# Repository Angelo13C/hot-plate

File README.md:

# Hot plate
An hot plate used to reflow solder electrical components on a PCB.

This is a table of contents:

| Name  | Description |
| ------------- | ------------- |
| [Firmware](firmware)  | The software running on the hot plate, written in Rust  |
| [Electronics](electronics)  | The plate that will become hot (which is a PCB) and the controller board that controls the current going to the plate (a separate PCB based on a STM32 microcontroller)   |

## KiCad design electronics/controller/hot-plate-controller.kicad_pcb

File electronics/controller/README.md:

# Electronics
This is the electrical control board on which the firmware runs.

It's based on an `STM32F730R8T6`. The board receives stable `24V` from an external power supply unit and requires around `10A` of current.

On the board there's a switching regulator that converts the `24V` to `3.3V`, which is used by: `thermistors`, `display`, `MLX90614` and microcontroller.

## Schematic
This is the electrical schematic of the board:

## PCB
The PCB (dimensions: 52mm x 52mm) has 4 layers (PWR/SIGNAL, GND, GND, PWR/SIGNAL). This is an image of the top layer:

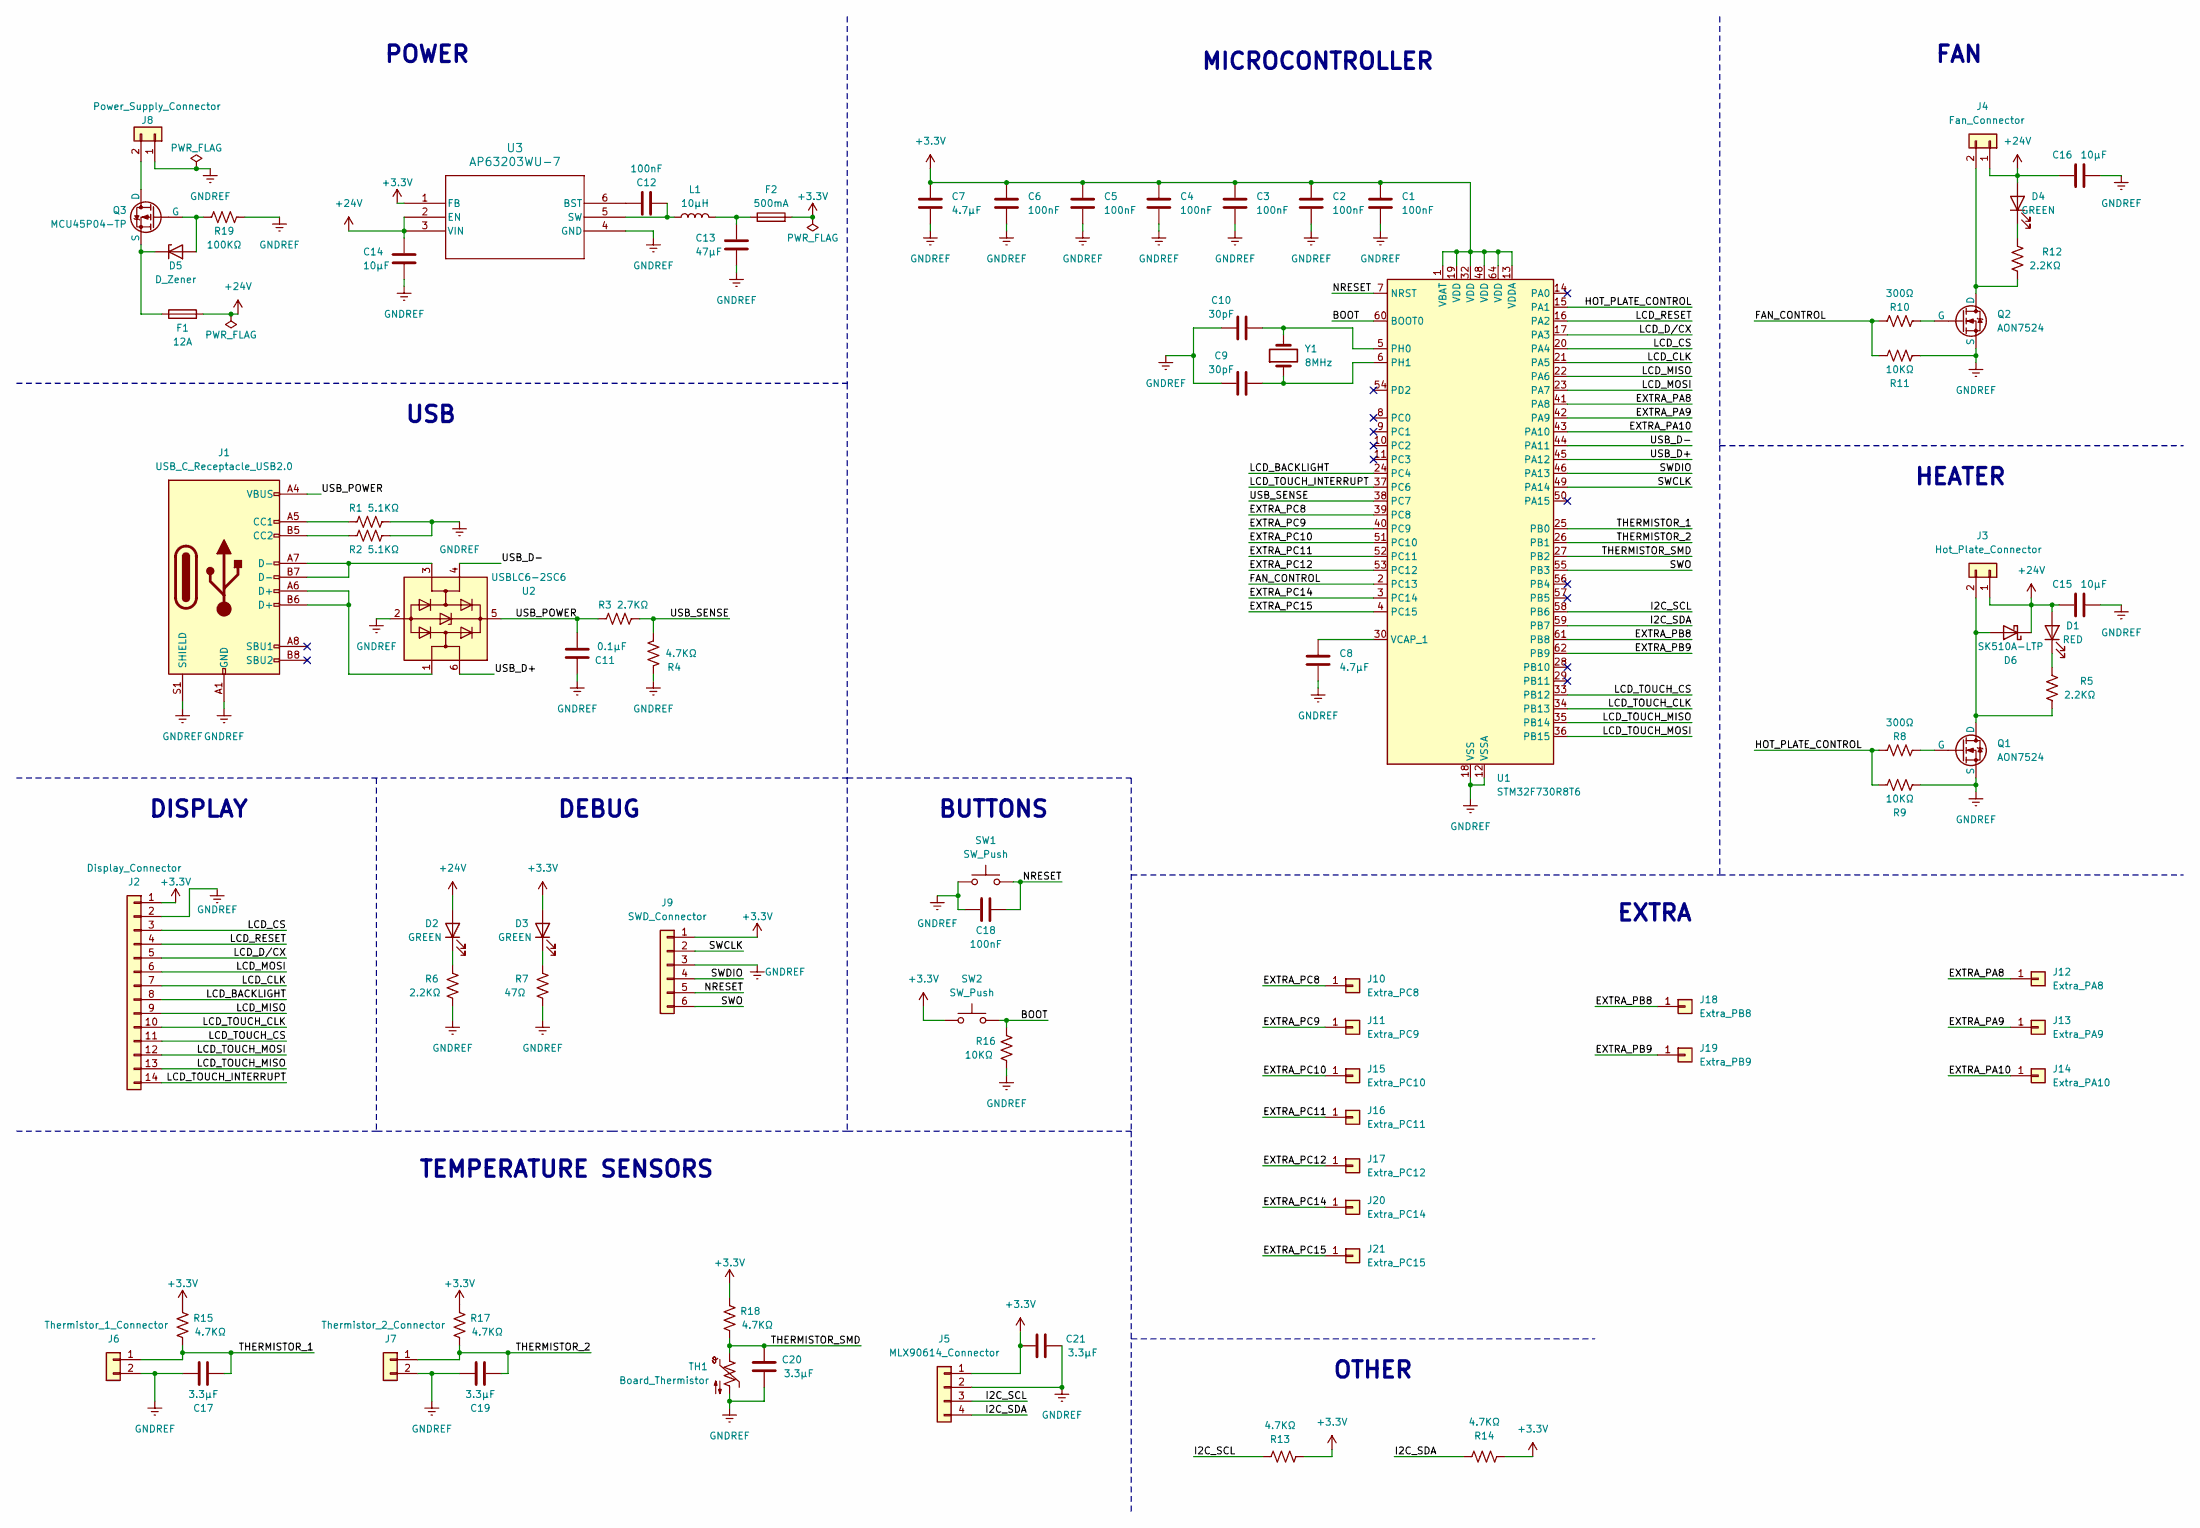
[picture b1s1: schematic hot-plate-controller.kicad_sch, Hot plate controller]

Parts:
C1, C2, C3, C4, C5, C6, C12, C18: 100nF; C_0805_2012Metric_Pad1.18x1.45mm_HandSolder
C7, C8: 4.7μF; C_0805_2012Metric_Pad1.18x1.45mm_HandSolder
C9, C10: 30pF; C_0805_2012Metric_Pad1.18x1.45mm_HandSolder
C11: 0.1μF; C_0805_2012Metric_Pad1.18x1.45mm_HandSolder
C13: 47μF; C_0805_2012Metric_Pad1.18x1.45mm_HandSolder
C14, C15, C16: 10μF; C_0805_2012Metric_Pad1.18x1.45mm_HandSolder
C17, C19, C20, C21: 3.3μF; C_0805_2012Metric_Pad1.18x1.45mm_HandSolder
D1: RED; LED_0603_1608Metric_Pad1.05x0.95mm_HandSolder
D2, D3, D4: GREEN; LED_0603_1608Metric_Pad1.05x0.95mm_HandSolder
D5: D_Zener; D_SOD-123
D6: SK510A-LTP; SMADO-214AC_LEAD-FRAME_MCC-L
F1: 12A; Fuse_1206_3216Metric_Pad1.42x1.75mm_HandSolder
F2: 500mA; Fuse_1206_3216Metric_Pad1.42x1.75mm_HandSolder
J1: USB_C_Receptacle_USB2.0; USB_C_Receptacle_GCT_USB4085
J2: Display_Connector; PinHeader_1x14_P2.54mm_Vertical
J3: Hot_Plate_Connector; PinHeader_1x02_P2.54mm_Vertical
J4: Fan_Connector; PinHeader_1x02_P2.54mm_Vertical
J5: MLX90614_Connector; PinHeader_1x04_P2.54mm_Vertical
J6: Thermistor_1_Connector; PinHeader_1x02_P2.54mm_Vertical
J7: Thermistor_2_Connector; PinHeader_1x02_P2.54mm_Vertical
J8: Power_Supply_Connector; PinHeader_1x02_P2.54mm_Vertical
J9: SWD_Connector; PinHeader_1x06_P2.54mm_Vertical
J10: Extra_PC8; PinHeader_1x01_P2.54mm_Vertical
J11: Extra_PC9; PinHeader_1x01_P2.54mm_Vertical
J12: Extra_PA8; PinHeader_1x01_P2.54mm_Vertical
J13: Extra_PA9; PinHeader_1x01_P2.54mm_Vertical
J14: Extra_PA10; PinHeader_1x01_P2.54mm_Vertical
J15: Extra_PC10; PinHeader_1x01_P2.54mm_Vertical
J16: Extra_PC11; PinHeader_1x01_P2.54mm_Vertical
J17: Extra_PC12; PinHeader_1x01_P2.54mm_Vertical
J18: Extra_PB8; PinHeader_1x01_P2.54mm_Vertical
J19: Extra_PB9; PinHeader_1x01_P2.54mm_Vertical
J20: Extra_PC14; PinHeader_1x01_P2.54mm_Vertical
J21: Extra_PC15; PinHeader_1x01_P2.54mm_Vertical
L1: 10μH; HPC 5040NF-100M
Q1, Q2: AON7524; DFN-8-1EP_3x3mm_P0.65mm_EP1.55x2.4mm
Q3: MCU45P04-TP; TO-252-2
R1, R2: 5.1KΩ; R_0805_2012Metric_Pad1.20x1.40mm_HandSolder
R3: 2.7KΩ; R_0805_2012Metric_Pad1.20x1.40mm_HandSolder
R4, R13, R14, R15, R17, R18: 4.7KΩ; R_0805_2012Metric_Pad1.20x1.40mm_HandSolder
R5, R6, R12: 2.2KΩ; R_0805_2012Metric_Pad1.20x1.40mm_HandSolder
R7: 47Ω; R_0805_2012Metric_Pad1.20x1.40mm_HandSolder
R8, R10: 300Ω; R_0805_2012Metric_Pad1.20x1.40mm_HandSolder
R9, R11, R16: 10KΩ; R_0805_2012Metric_Pad1.20x1.40mm_HandSolder
R19: 100KΩ; R_0805_2012Metric_Pad1.20x1.40mm_HandSolder
SW1, SW2: SW_Push; SW_LS38J2F-T
TH1: Board_Thermistor; R_0805_2012Metric_Pad1.20x1.40mm_HandSolder
U1: STM32F730R8T6; LQFP-64_10x10mm_P0.5mm
U2: USBLC6-2SC6; SOT-23-6_Handsoldering
U3: AP63203WU-7; AP63203WU-7_DIO
Y1: 8MHz; Crystal_HC49-4H_Vertical

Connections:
+3.3V: C1.1, C2.1, C3.1, C4.1, C5.1, C6.1, C7.1, C21.2, D3.2 (A), F2.2, J2.1, J5.1, J9.1, R13.1, R14.1, R15.1, R17.1, R18.1, SW2.1, U1.1 (VBAT), U1.13 (VDDA), U1.19 (VDD), U1.32 (VDD), U1.48 (VDD), U1.64 (VDD), U3.1 (FB)
+24V: C14.1, C15.1, C16.1, D1.2 (A), D2.2 (A), D4.2 (A), D6.1 (K), F1.2, J3.1, J4.1, U3.2 (EN), U3.3 (VIN)
/BOOT: R16.1, SW2.2, U1.60 (BOOT0)
/EXTRA_PA8: J12.1, U1.41 (PA8)
/EXTRA_PA9: J13.1, U1.42 (PA9)
/EXTRA_PA10: J14.1, U1.43 (PA10)
/EXTRA_PB8: J18.1, U1.61 (PB8)
/EXTRA_PB9: J19.1, U1.62 (PB9)
/EXTRA_PC8: J10.1, U1.39 (PC8)
/EXTRA_PC9: J11.1, U1.40 (PC9)
/EXTRA_PC10: J15.1, U1.51 (PC10)
/EXTRA_PC11: J16.1, U1.52 (PC11)
/EXTRA_PC12: J17.1, U1.53 (PC12)
/EXTRA_PC14: J20.1, U1.3 (PC14)
/EXTRA_PC15: J21.1, U1.4 (PC15)
/FAN_CONTROL: R10.2, R11.2, U1.2 (PC13)
/HOT_PLATE_CONTROL: R8.2, R9.2, U1.15 (PA1)
/I2C_SCL: J5.3, R13.2, U1.58 (PB6)
/I2C_SDA: J5.4, R14.2, U1.59 (PB7)
/LCD_BACKLIGHT: J2.8, U1.24 (PC4)
/LCD_CLK: J2.7, U1.21 (PA5)
/LCD_CS: J2.3, U1.20 (PA4)
/LCD_D/CX: J2.5, U1.17 (PA3)
/LCD_MISO: J2.9, U1.22 (PA6)
/LCD_MOSI: J2.6, U1.23 (PA7)
/LCD_RESET: J2.4, U1.16 (PA2)
/LCD_TOUCH_CLK: J2.10, U1.34 (PB13)
/LCD_TOUCH_CS: J2.11, U1.33 (PB12)
/LCD_TOUCH_INTERRUPT: J2.14, U1.37 (PC6)
/LCD_TOUCH_MISO: J2.13, U1.35 (PB14)
/LCD_TOUCH_MOSI: J2.12, U1.36 (PB15)
/NRESET: C18.2, J9.5, SW1.2, U1.7 (NRST)
/SWCLK: J9.2, U1.49 (PA14)
/SWDIO: J9.4, U1.46 (PA13)
/SWO: J9.6, U1.55 (PB3)
/THERMISTOR_1: C17.2, J6.1, R15.2, U1.25 (PB0)
/THERMISTOR_2: C19.2, J7.1, R17.2, U1.26 (PB1)
/THERMISTOR_SMD: C20.2, R18.2, TH1.1, U1.27 (PB2)
/USB_D+: U1.45 (PA12), U2.6 (I/O1)
/USB_D-: U1.44 (PA11), U2.4 (I/O2)
/USB_POWER: C11.2, J1.A4 (VBUS), J1.A9 (VBUS), J1.B4 (VBUS), J1.B9 (VBUS), R3.1, U2.5 (VBUS)
/USB_SENSE: R3.2, R4.1, U1.38 (PC7)
GNDREF: C1.2, C2.2, C3.2, C4.2, C5.2, C6.2, C7.2, C8.2, C9.1, C10.1, C11.1, C13.2, C14.2, C15.2, C16.2, C17.1, C18.1, C19.1, C20.1, C21.1, J1.A1 (GND), J1.A12 (GND), J1.B1 (GND), J1.B12 (GND), J1.S1 (SHIELD), J2.2, J5.2, J6.2, J7.2, J8.1, J9.3, Q1.3 (S), Q2.3 (S), R1.2, R2.2, R4.2, R6.2, R7.2, R9.1, R11.1, R16.2, R19.2, SW1.1, TH1.2, U1.12 (VSSA), U1.18 (VSS), U1.31 (VSS), U1.47 (VSS), U1.63 (VSS), U2.2 (GND), U3.4 (GND)
unnamed: C13.1, F2.1, L1.2
unnamed: D1.1 (K), R5.1
unnamed: D2.1 (K), R6.1
unnamed: D3.1 (K), R7.1
unnamed: D4.1 (K), R12.1
unnamed: D5.2 (A), Q3.2 (G), R19.1
unnamed: D5.1 (K), F1.1, Q3.3 (S)
unnamed: D6.2 (A), J3.2, Q1.1 (D), R5.2
unnamed: J1.A5 (CC1), R1.1
unnamed: J1.B5 (CC2), R2.1
unnamed: J1.A6 (D+), J1.B6 (D+), U2.1 (I/O1)
unnamed: J1.A7 (D-), J1.B7 (D-), U2.3 (I/O2)
unnamed: J4.2, Q2.1 (D), R12.2
unnamed: J8.2, Q3.1 (D)
unnamed: Q1.2 (G), R8.1
unnamed: Q2.2 (G), R10.1
unnamed: C10.2, U1.5 (PH0), Y1.2
unnamed: C9.2, U1.6 (PH1), Y1.1
unnamed: C8.1, U1.30 (VCAP_1)
unnamed: C12.1, U3.6 (BST)
unnamed: C12.2, L1.1, U3.5 (SW)

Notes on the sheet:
DEBUG
POWER
DISPLAY
MICROCONTROLLER
USB
BUTTONS
HEATER
OTHER
FAN
EXTRA
TEMPERATURE SENSORS

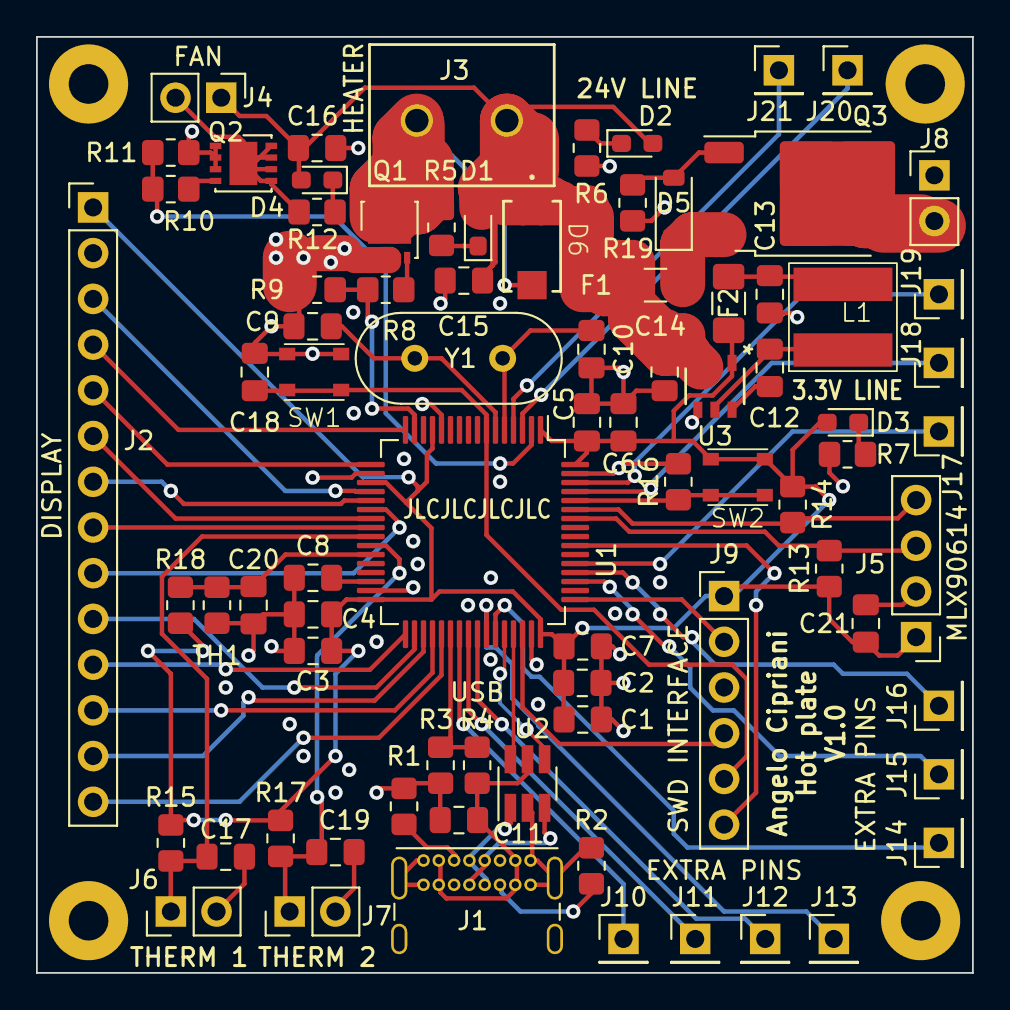
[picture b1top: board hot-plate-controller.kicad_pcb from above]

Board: 4 copper layers, 52.0 x 52.0 mm, 80 parts (0 on the bottom side), 64 nets.

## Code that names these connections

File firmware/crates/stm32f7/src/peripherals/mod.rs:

use cortex_m::Peripherals as CortexPeripherals;
use firmware_core::hot_plate::peripherals::Peripherals as PeripheralsTrait;
use stm32f7xx_hal::{
	gpio::{GpioExt, Output, Pin},
	pac::{Peripherals as Stm32Peripherals, SPI1, TIM1, TIM8},
	prelude::*,
	rcc::{HSEClock, HSEClockMode},
	timer::*,
};

use self::{pwm::PwmPin, system_time::SystemTime};

mod pwm;
mod system_time;

pub struct Peripherals {
	lcd_dcx_pin: Option<<Self as PeripheralsTrait>::LcdDCXPin>,
	lcd_reset_pin: Option<<Self as PeripheralsTrait>::LcdResetPin>,
	lcd_spi: Option<<Self as PeripheralsTrait>::LcdSpi>,

	fan_pin: Option<<Self as PeripheralsTrait>::FanPin>,
	heater_pin: Option<<Self as PeripheralsTrait>::HeaterPin>,
	adc: Option<<Self as PeripheralsTrait>::ADC>,
	thermistor1_pin: Option<<Self as PeripheralsTrait>::Thermistor1Pin>,

	system_time: Option<<Self as PeripheralsTrait>::SystemTime>,
}

impl PeripheralsTrait for Peripherals {
	type LcdDCXPin = Pin<'A', 3, Output>;

	type LcdResetPin = Pin<'A', 2, Output>;

	type LcdSpi = SPI1;

	type FanPin = PwmPin<TIM1, C1>;

	type HeaterPin = PwmPin<TIM8, C1>;

	type ADC;

	type Thermistor1Pin;

	type SystemTime = SystemTime<1_000_000>;

	fn take_lcd_dcx_pin(&mut self) -> Option<Self::LcdDCXPin> {
		self.lcd_dcx_pin.take()
	}

	fn take_lcd_reset_pin(&mut self) -> Option<Self::LcdResetPin> {
		self.lcd_reset_pin.take()
	}

	fn take_lcd_spi(&mut self) -> Option<Self::LcdSpi> {
		self.lcd_spi.take()
	}

	fn take_fan_pin(&mut self) -> Option<Self::FanPin> {
		self.fan_pin.take()
	}

	fn take_heater_pin(&mut self) -> Option<Self::HeaterPin> {
		self.heater_pin.take()
	}

	fn take_adc(&mut self) -> Option<Self::ADC> {
		self.adc.take()
	}

	fn take_thermistor1_pin(&mut self) -> Option<Self::Thermistor1Pin> {
		self.thermistor1_pin.take()
	}

	fn take_system_time(&mut self) -> Option<Self::SystemTime> {
		self.system_time.take()
	}
}

impl Peripherals {
	pub fn from_stm32_peripherals(stm_peripherals: Stm32Peripherals, cortex_peripherals: CortexPeripherals) -> Self {
		let gpio_a = stm_peripherals.GPIOA.split();
		let gpio_c = stm_peripherals.GPIOC.split();

		let rcc = stm_peripherals.RCC.constrain();
		let clocks = rcc
			.cfgr
			.hse(HSEClock::new(8.MHz(), HSEClockMode::Oscillator))
			.sysclk(216.MHz())
			.freeze();

		let heater_pwm = stm_peripherals
			.TIM1
			.pwm_hz(gpio_a.pa1.into_alternate(), 2.kHz(), &clocks)
			.split();

		let system_time = Timer::syst(cortex_peripherals.SYST, &clocks).counter_us();

		Self {
			lcd_dcx_pin: Some(gpio_a.pa3.into_push_pull_output()),
			lcd_reset_pin: Some(gpio_a.pa2.into_push_pull_output()),
			lcd_spi: Some(stm_peripherals.SPI1),
			fan_pin: Some(gpio_c.pc13.into_alternate()),
			heater_pin: Some(PwmPin::new(heater_pwm)),
			adc: Some(),
			thermistor1_pin: Some(),
			system_time: Some(),
		}
	}
}

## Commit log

2023-12-22 🎉 Initial commit
2023-12-22 🎉 Begin the electronics hot-plate-controller project
2023-12-26 🍱 Add the "Project" symbol library on KiCad
2023-12-26 🍱 Add the "Project" footprint library on KiCad
2023-12-26 🍱 Add the symbols for all the components used in the project on KiCad
2023-12-26 🍱 Add the USB C footprint on KiCad
2023-12-26 🍱 Add the PMOS footprint on KiCad
2023-12-26 🍱 Add the Button footprint on KiCad
2023-12-26 🍱 Add the SOT-23-6 footprint on KiCad
2023-12-26 🍱 Add the Resistor footprint on KiCad
2023-12-26 🍱 Add the footprints for pin headers on KiCad
2023-12-26 🍱 Add the STM32 footprint on KiCad
2023-12-26 🍱 Add the LED footprint on KiCad
2023-12-26 🍱 Add the footprint for an inductor on KiCad
2023-12-26 🍱 Add the footprint for a fuse (1206) on KiCad
2023-12-26 🍱 Add the NMOS footprint on KiCad
2023-12-26 🍱 Add the Crystal oscillator footprint on KiCad
2023-12-26 🍱 Add the footprint for a capacitor (0805) on KiCad
2023-12-26 🍱 Add the D_SOD-123 footprint on KiCad
2023-12-26 🍱 Add the AP63203WU-7 footprint on KiCad
2023-12-26 🎉 Begin the electronics hot-plate project
2023-12-26 🍱 Add the connector footprint to the hot-plate on KiCad
2023-12-26 🍱 Add the connector symbol to the hot-plate on KiCad
2023-12-26 🧑‍💻 Create a Python tool to automatically generate the trace of the hot plate given some parameters
2023-12-27 🍱 Add the mounting hole footprint to the controller in KiCad
2023-12-27 🍱 Add the Fuse_0603 footprint to the controller in KiCad
2023-12-27 🍱 Add the Resistor_1206 footprint to the controller in KiCad
2023-12-27 🍱 Add the SMADO-214AC_LEAD footprint to the controller in KiCad
2023-12-27 🍱 Update the footprint of the button in the controller on KiCad
    The button is now smaller
2023-12-27 🍱 Add the Schottky diode symbol to the controller in KiCad
2023-12-27 🎉 Begin the firmware-stm32 project
    This is based on the start guide at this link: https://github.com/rust-embedded/cortex-m-quickstart
2023-12-27 ⬆️ Upgrade various dependencies of the firmware-stm32 crate
2023-12-27 🎨 Start using rustfmt to format all the code
2023-12-27 🙈 .gitignore some things at the root directory of the firmware project
2023-12-27 🎉 Begin the firmware-core project
2023-12-27 ➕ Add the firmware-core dependency to firmware-stm32
2023-12-29 🍱 Add some symbols to the controller on KiCad
2023-12-29 🍱 Add the footprint of a pin header (1x01) to the controller on KiCad
2023-12-29 🍱 Add the footprint of a pin header (1x06) to the controller on KiCad
2023-12-29 🍱 Add the footprint of a terminal block to the controller on KiCad
2023-12-29 🍱 Modify the footprint of the USB-C receptacle in the controller on KiCad
2023-12-29 🍱 Modify the footprint of the button in the controller on KiCad
2023-12-29 🍱 Modify the "SMADO-214AC_LEAD-FRAME_MCC-L" footprint in the controller on KiCad
2023-12-29 ✨ Create the schematic of the hot-plate
2023-12-29 ✨ Create the PCB layout of the hot-plate
2023-12-29 ✨ Create the whole schematic of the hot-plate-controller
2023-12-29 ✨ Create the whole PCB layout of the hot-plate-controller
2023-12-29 ➕ Add the embedded-hal dependency to firmware-core
2023-12-29 ➕ Add the ringbuffer dependency to firmware-core
2023-12-29 ➕ Add the micromath dependency to firmware-core
2023-12-29 ➕ Add the enumset dependency to firmware-core
2023-12-29 ➕ Add the pid dependency to firmware-core
2023-12-29 ✨ Add some utils functions to firmware-core
2023-12-29 🙈 Gitignore some files in the firmware-stm32f7 crate
2023-12-29 📝 Add a README file to electronics
2023-12-29 👷 Add GitHub CI system
2024-04-08 🙈 Add the fabrication files to the .gitignore
2024-04-08 🔧 Update the project file of the controller in KiCad
2024-05-29 📝 Add a README file to the repository
2024-05-29 📝 Update the README file
2024-05-29 ✨ Add most of the functionalities to the firmware
